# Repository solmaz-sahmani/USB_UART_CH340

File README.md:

# USB UART CH340

A custom **USB-to-UART converter** designed in **KiCad** using the **CH340** USB-to-serial interface.

This project was created as a practical PCB design project to gain hands-on experience with schematic design, PCB layout, component placement, routing, and hardware interfacing for embedded systems.

## 📷 Board

## 🔧 Features

* USB to UART communication
* CH340 USB-to-Serial interface
* UART TX/RX interface
* Designed for embedded development and debugging
* Custom PCB designed in KiCad
* Compact and practical development tool

The CH340 provides a USB interface on the computer side and a hardware full-duplex serial interface on the MCU side.

## 🛠️ Hardware

| Component          | Description                        |
| ------------------ | ---------------------------------- |
| CH340              | USB-to-UART interface              |
| USB connector      | USB connection to PC               |
| UART header        | TX / RX / VCC / GND interface      |
| LEDs               | Communication / status indication  |
| Passive components | Decoupling and interface circuitry |

## 💻 Applications

This board can be used as a USB-to-UART interface for embedded development, debugging, and serial communication with microcontrollers such as:

* STM32
* ESP32
* AVR
* Arduino
* Other UART-based embedded systems

USB-to-UART converters are commonly used to communicate with microcontrollers and can also be used for firmware programming when the target hardware supports the required boot/programming interface.

## 📐 Design

The complete hardware design was developed in **KiCad**, including:

* Schematic design
* Component selection
* PCB layout
* Routing
* Design verification
* PCB manufacturing files

### Project Files

```text
USB_UART_CH340/
├── USB_UART_CH340.kicad_pro
├── USB_UART_CH340.kicad_sch
├── USB_UART_CH340.kicad_pcb
├── USB_UART_CH340.kicad_prl
├── images/
│   └── board.jpg
└── README.md
```

## 📚 Learning Objectives

This project was developed to strengthen practical skills in:

* PCB design with KiCad
* USB-to-UART interfaces
* UART communication
* Hardware design for embedded systems
* Schematic capture
* PCB layout and routing
* Component placement
* Hardware debugging

## 🚧 Project Status

**Completed**

The KiCad schematic and PCB design are available in this repository.

## 📌 Future Improvements

Possible future revisions may include:

* 3.3 V / 5 V selectable UART levels
* Automatic boot/reset circuitry for supported MCUs
* ESD protection
* Improved USB protection
* Smaller PCB footprint
* Additional UART control signals

## 📄 License

This project is provided for educational and personal development purposes.

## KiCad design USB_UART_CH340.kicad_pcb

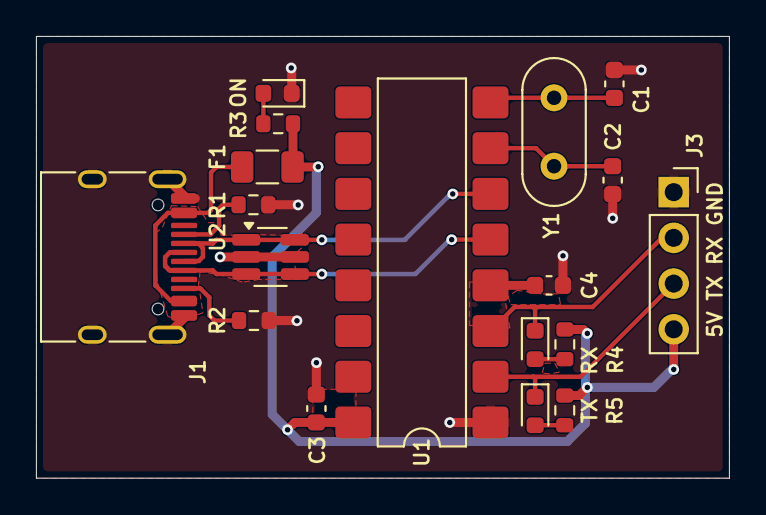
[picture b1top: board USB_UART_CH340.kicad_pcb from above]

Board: 2 copper layers, 38.5 x 24.5 mm, 18 parts (0 on the bottom side), 15 nets.

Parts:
C1, C2: 22pF; C_0603_1608Metric
C3, C4: 100nF; C_0603_1608Metric
F1: 500mA; Fuse_1206_3216Metric
J1: USB_C_Receptacle_USB2.0_16P; USB_C_Receptacle_HRO_TYPE-C-31-M-12
J3: Conn_01x04_Pin; PinSocket_1x04_P2.54mm_Vertical
ON: LED; LED_0603_1608Metric
R1, R2: 5.1kΩ; R_0603_1608Metric
R3, R4, R5: 1kΩ; R_0603_1608Metric
RX: LED; LED_0603_1608Metric
TX: LED; LED_0603_1608Metric
U1: CH340G; SMDIP-16_W7.62mm
U2: USBLC6-2P6; SOT-23-6_Handsoldering
Y1: 12MHz; Crystal_HC52-6mm_Vertical

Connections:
/RX: J3.2, RX.1 (K), U1.3 (RXD)
/TX: J3.3, TX.1 (K), U1.2 (TXD)
/USB_5V: C3.2, F1.2, J3.4, R3.1, R4.2, R5.2, U1.16 (VCC)
/USB_D+: J1.A6 (D+), J1.B6 (D+), U1.5 (UD+), U2.3 (I/O2), U2.4 (I/O2)
/USB_D-: J1.A7 (D-), J1.B7 (D-), U1.6 (UD-), U2.1 (I/O1), U2.6 (I/O1)
/XI: C2.1, U1.7 (XI), Y1.2
/XO: C1.1, U1.8 (XO), Y1.1
GND: C1.2, C2.2, C3.1, C4.1, J1.A1 (GND), J1.A12 (GND), J1.B1 (GND), J1.B12 (GND), J1.SH (SHIELD), J3.1, ON.1 (K), R1.2, R2.2, U1.1 (GND), U2.2 (GND), U2.5 (VBUS)
unnamed: ON.2 (A), R3.2
unnamed: R5.1, TX.2 (A)
unnamed: R4.1, RX.2 (A)
unnamed: F1.1, J1.A4 (VBUS), J1.A9 (VBUS), J1.B4 (VBUS), J1.B9 (VBUS)
unnamed: J1.A5 (CC1), R1.1
unnamed: J1.B5 (CC2), R2.1
unnamed: C4.2, U1.4 (V3)
